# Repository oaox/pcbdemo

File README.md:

# pcbdemo
Demonstrates my way to structure Kicad projects, see detailed description in 

pcbdemo/doc/pcbdemo.pdf
.
Includes a few makefiles and scripts to help maintain the documentation
of the designed PCBs.

This project produces pdf and html files based on the kicad_pcb
file in addition to bom and component position files.

Uses Python, Asciidoc, Prince and asciidoctor.

Prince (https://www.princexml.com/) converts html/css files to pdf and
lets you produce pdfs formatted by the css. In this case I used the
default formatting.

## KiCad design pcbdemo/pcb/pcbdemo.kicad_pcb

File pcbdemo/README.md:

# pcbdemo
Demonstrates my way to structure Kicad projects, see detailed description in doc/pcbdemo.pdf
.
Includes a few makefiles and scripts to help maintain the documentation
of the designed PCBs.

This project produces pdf and html files based on the kicad_pcb
file in addition to bom and component position files.

Uses Python, Asciidoc, Prince and asciidoctor.

Prince (https://www.princexml.com/) converts html/css files to pdf and
lets you produce pdfs formatted by the css. In this case I used the
default formatting.

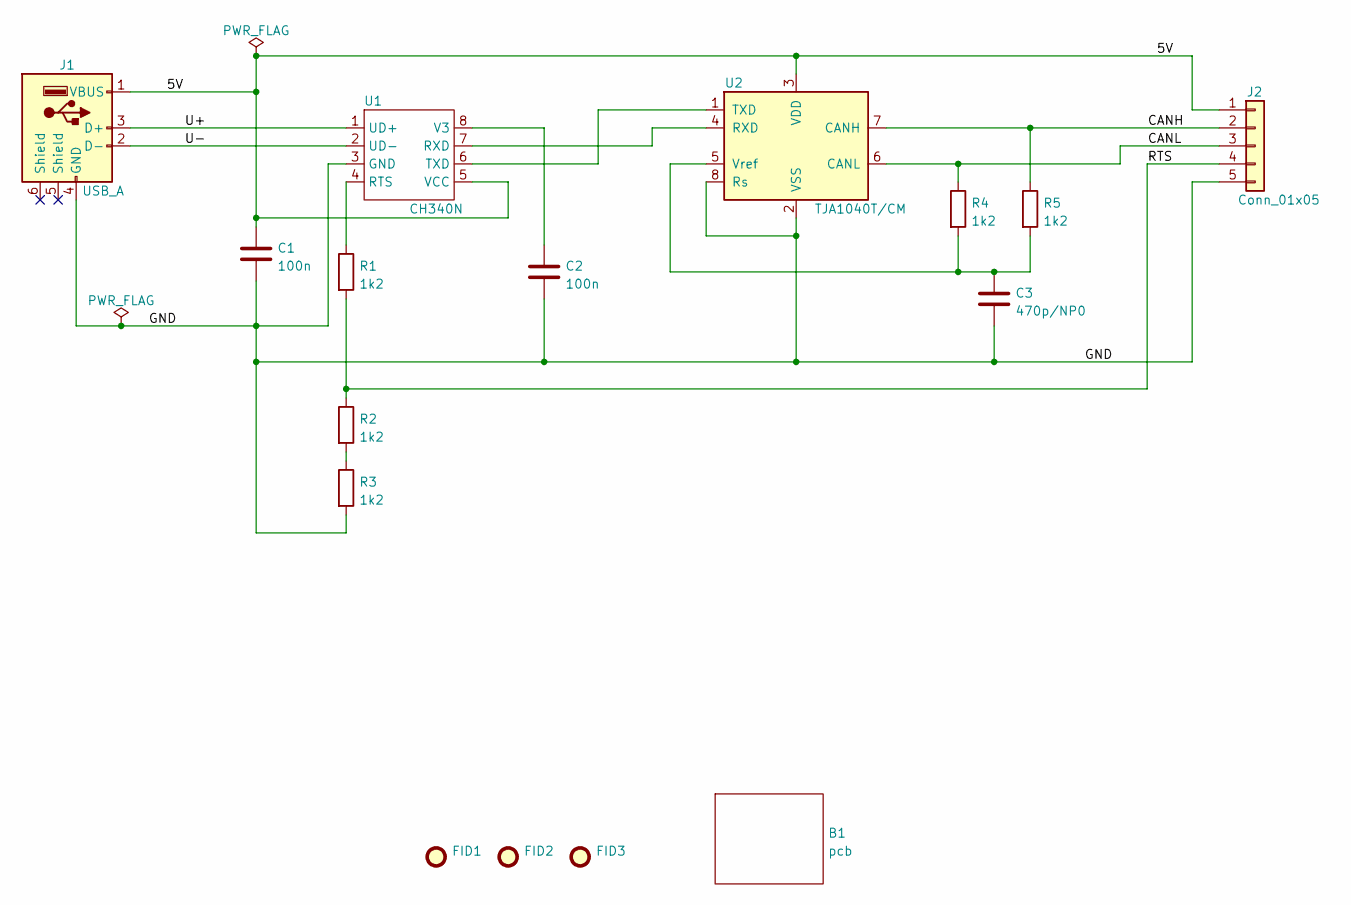
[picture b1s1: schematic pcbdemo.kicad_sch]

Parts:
B1: pcb; pcbUsbPlug
C1, C2: 100n; C_0603_1608Metric
C3: 470p/NP0; C_0603_1608Metric
FID1, FID2, FID3: Fiducial; Fiducial_1mm_Mask2mm
J1: USB_A; USBA-SHOUHAN-AM180
J2: Conn_01x05; PinHeader_1x05_P2.54mm_Vertical
R1, R2, R3, R4, R5: 1k2; R_0603_1608Metric
U1: CH340N; SO-8_3.9x4.9mm_P1.27mm
U2: TJA1040T/CM; SOP-8_3.9x4.9mm_P1.27mm

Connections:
/5V: C1.1, J1.1 (VBUS), J2.1, U1.5 (VCC), U2.3 (VDD)
/CANH: J2.2, R5.1, U2.7 (CANH)
/CANL: J2.3, R4.1, U2.6 (CANL)
/GND: C1.2, C2.2, C3.2, J1.4 (GND), J2.5, R3.2, U1.3 (GND), U2.2 (VSS), U2.8 (Rs)
/RTS: J2.4, R1.2, R2.1
/U+: J1.3 (D+), U1.1 (UD+)
/U-: J1.2 (D-), U1.2 (UD-)
unnamed: C2.1, U1.8 (V3)
unnamed: C3.1, R4.2, R5.2, U2.5 (Vref)
unnamed: R1.1, U1.4 (RTS)
unnamed: R2.2, R3.1
unnamed: U1.6 (TXD), U2.1 (TXD)
unnamed: U1.7 (RXD), U2.4 (RXD)

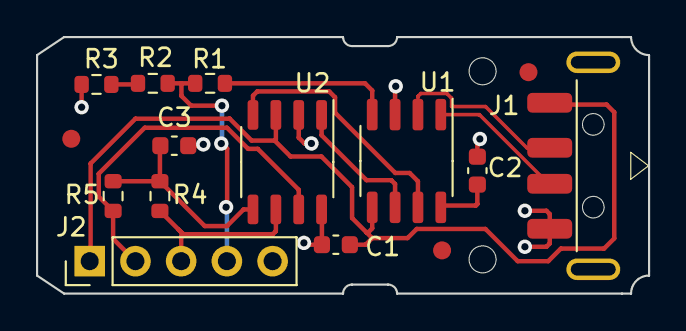
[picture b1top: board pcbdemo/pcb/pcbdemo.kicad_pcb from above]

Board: 2 copper layers, 34.0 x 14.2 mm, 16 parts (0 on the bottom side), 13 nets.

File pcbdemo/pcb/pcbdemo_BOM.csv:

Ref, Value, Vendor, SKU
C1,                100n,     elfa          ,      321         
C2,                100n,               ,             
C3,                470p/NP0,        digikey   ,       1234        
J1,                USB_A,               ,               
R1,                1k2,               ,               
R2,                1k2,               ,               
R3, 1k2, , 
R4, 1k2, , 
R5, 1k2, , 
U1,                CH340N,               ,               
U2,                TJA1040T/CM,               ,

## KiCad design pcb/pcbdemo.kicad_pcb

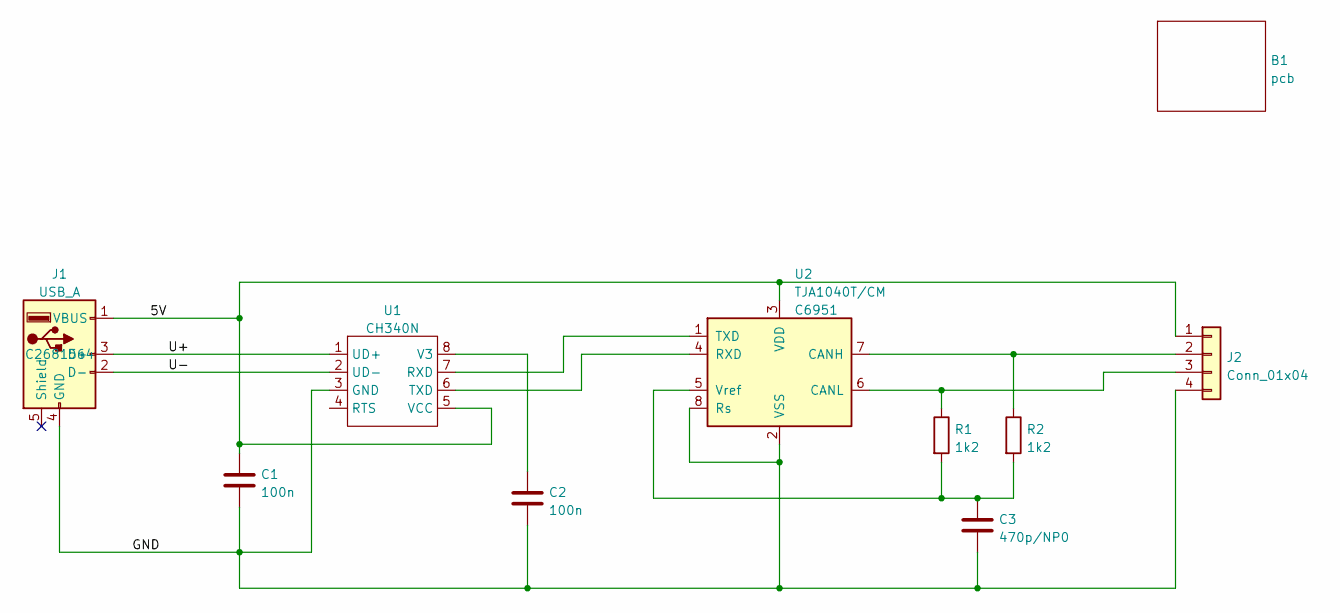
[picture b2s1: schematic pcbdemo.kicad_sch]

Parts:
B1: pcb; pcbUsbPlug
C1, C2: 100n; C_0603_1608Metric; LCSC C14663
C3: 470p/NP0; C_0603_1608Metric; LCSC C1620
J1: USB_A; USBA-SHOUHAN-AM180; LCSC C2681564
J2: Conn_01x04; PinHeader_1x04_P2.54mm_Vertical
R1, R2: 1k2; R_0603_1608Metric; LCSC C22765
U1: CH340N; SO-8_3.9x4.9mm_P1.27mm; LCSC C2977777
U2: TJA1040T/CM; SOIC-8_3.9x4.9mm_P1.27mm; LCSC C6951

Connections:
/5V: C1.1, J1.1 (VBUS), J2.1, U1.5 (VCC), U2.3 (VDD)
/GND: C1.2, C2.2, C3.2, J1.4 (GND), J2.4, U1.3 (GND), U2.2 (VSS), U2.8 (Rs)
/U+: J1.3 (D+), U1.1 (UD+)
/U-: J1.2 (D-), U1.2 (UD-)
unnamed: C2.1, U1.8 (V3)
unnamed: C3.1, R1.2, R2.2, U2.5 (Vref)
unnamed: J2.2, R2.1, U2.7 (CANH)
unnamed: J2.3, R1.1, U2.6 (CANL)
unnamed: U1.6 (TXD), U2.4 (RXD)
unnamed: U1.7 (RXD), U2.1 (TXD)

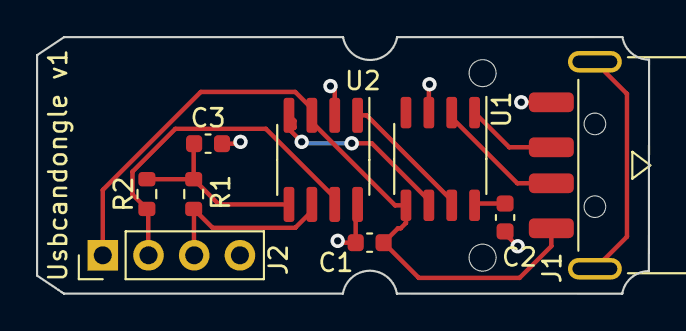
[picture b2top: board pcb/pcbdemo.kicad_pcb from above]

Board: 2 copper layers, 34.0 x 14.3 mm, 10 parts (0 on the bottom side), 10 nets.

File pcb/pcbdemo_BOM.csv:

Ref, Value, Vendor, SKU
B1,             pcb,            ,            
C1,             100n,  elfa          ,   321         
C2,             100n,            ,          
C3,             470p/NP0,     digikey   ,    1234        
J1,             USB_A,            ,            
J2,             Conn_01x04,            ,            
R1,             1k2,            ,            
R2,             1k2,            ,            
U1,             CH340N,            ,            
U2,             TJA1040T/CM,            ,

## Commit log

2022-09-20 Changes to bot make files and kicad files
2022-10-15 Add files via upload
    Added script directory
2022-10-15 Add files via upload
    Added pcbdemo directory
2022-10-15 Delete doc directory
    Deleted directory uploaded to wrong point
2022-10-15 Delete pcb directory
    Deleted directory uploaded to wrong point
2022-10-15 Update README.md
    Trying a html link
2022-10-15 Update README.md
    Trying html link
2022-10-15 Update README.md
    Try local html perma link
2022-10-17 Update before publication
2022-10-17 Edited the README file
2022-10-17 Fixed README
2022-10-17 Edited the doc/pcbdemo.adoc file
